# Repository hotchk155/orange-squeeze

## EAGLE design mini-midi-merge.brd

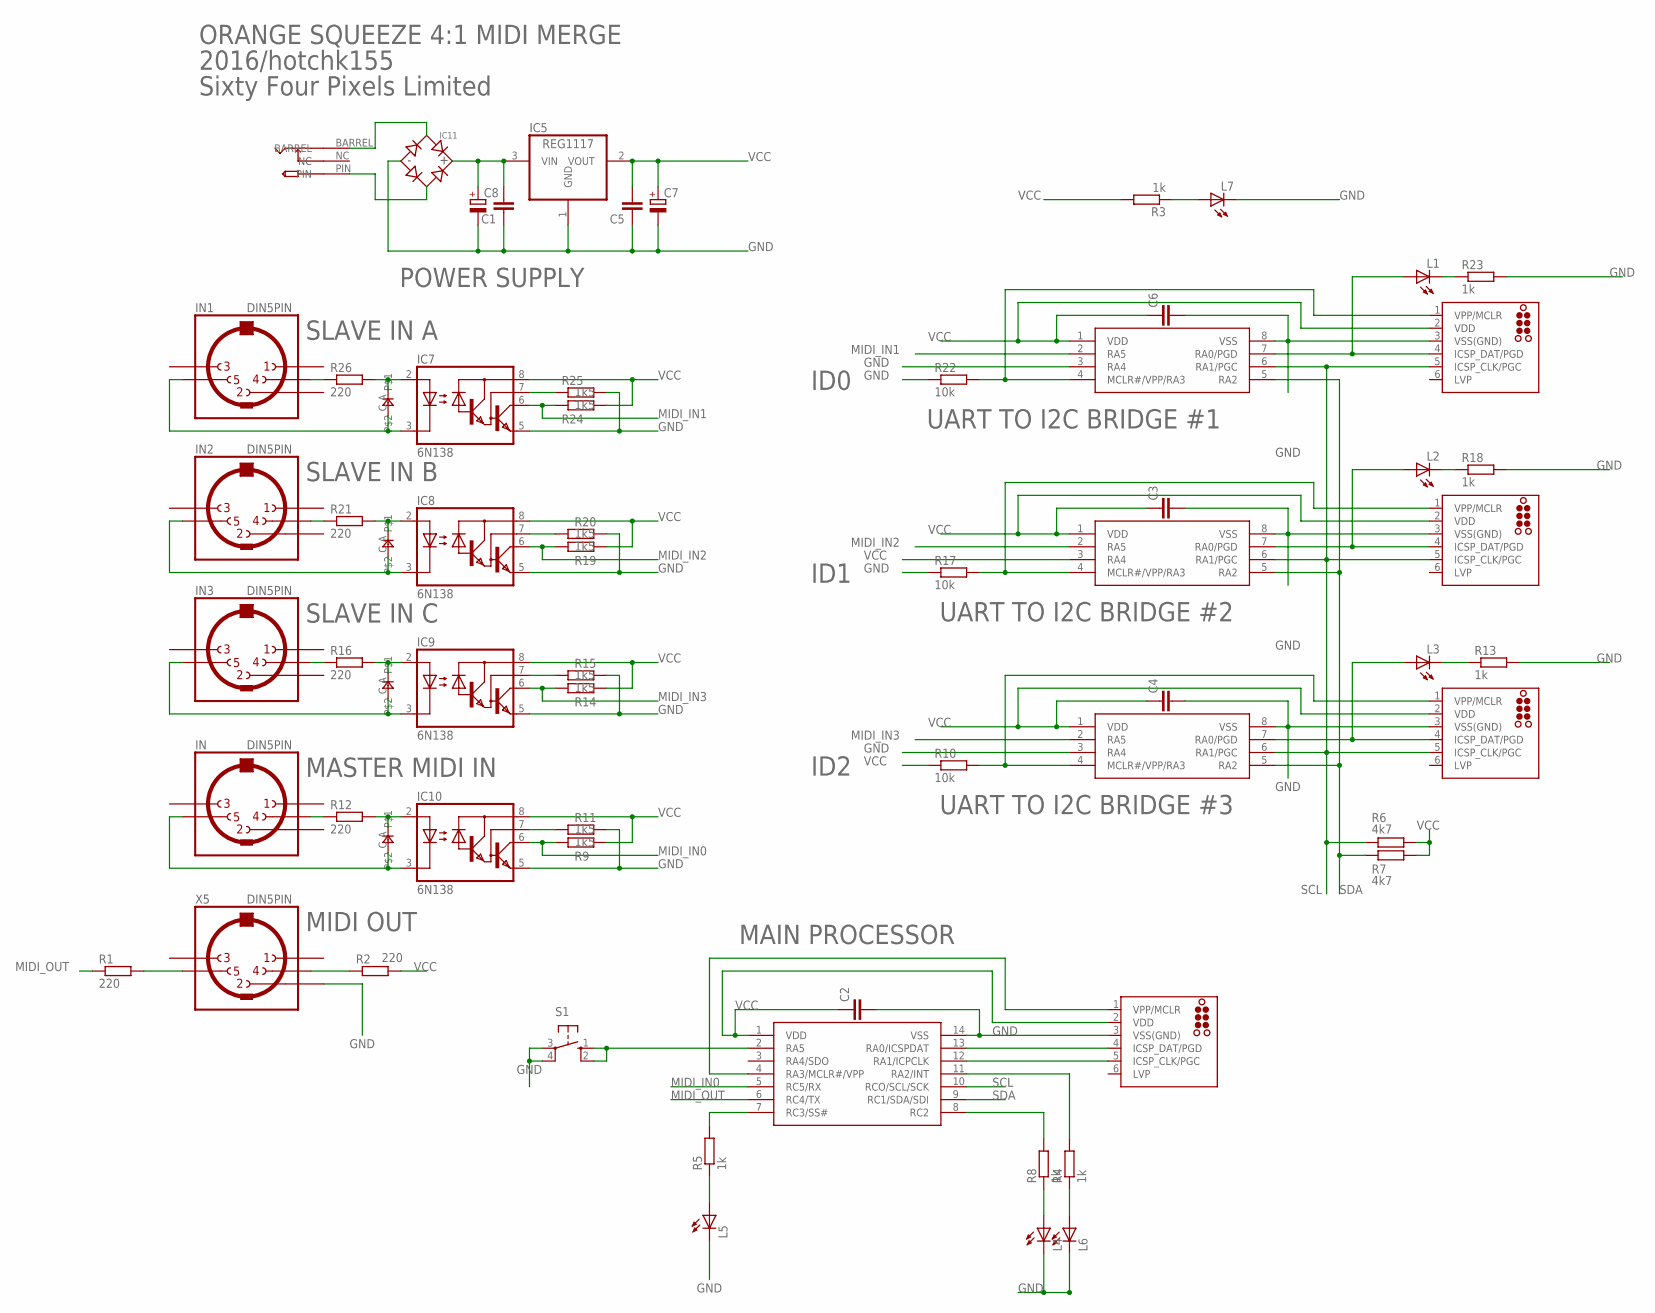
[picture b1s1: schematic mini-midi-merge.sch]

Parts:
C1, C2, C3, C4, C5, C6: C-EUC0805; C0805
C7, C8: CPOL-EUE2,5-6E; E2,5-6E
D1, D2, D3, D4: 0805DIODE
IC1: PIC16F1825SO14; SO14
IC2, IC3, IC4: PIC12F1822SO08; SO08
IC5: REG1117; SOT223
IC7, IC8, IC9, IC10: 6N138; DIL08
IC11: BRIDGERECTIFIER; SOIC-4
ICSP1, ICSP2, ICSP3, ICSP4: TC2030-MCP-NL
IN, IN1, IN2, IN3: DIN5PIN; EDGEDIN
L1, L2, L3, L4, L5, L6, L7: LED3MM
R1, R2, R12, R16, R21, R26: 220; R0805
R3, R4, R5, R8, R13, R18, R23: 1k; R0805
R6, R7: 4k7; R0805
R9, R11, R14, R15, R19, R20, R24, R25: 1k5; R0805
R10, R17, R22: 10k; R0805
S1: 10-XX; B3F-10XX
U$9: PWR_SOCKET_2_1MM
X5: DIN5PIN; EDGEDIN

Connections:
GND: C1.1, C2.2, C3.2, C4.2, C5.1, C6.2, C7.-, C8.-, IC1.14 (VSS), IC2.3 (RA4), IC2.8 (VSS), IC3.8 (VSS), IC4.3 (RA4), IC4.8 (VSS), IC5.1 (GND), IC7.5 (GND), IC8.5 (GND), IC9.5 (GND), IC10.5 (GND), IC11.-, ICSP1.3 (VSS(GND)), ICSP2.3 (VSS(GND)), ICSP3.3 (VSS(GND)), ICSP4.3 (VSS(GND)), L4.K (C), L5.K (C), L6.K (C), L7.K (C), R11.2, R13.2, R15.2, R17.1, R18.2, R20.2, R22.1, R23.2, R25.2, S1.3, S1.4 (P1), X5.2
MIDI_IN0: IC1.5 (RC5/RX), IC10.6 (VO), R9.1
MIDI_IN1: IC4.2 (RA5), IC7.6 (VO), R24.1
MIDI_IN2: IC3.2 (RA5), IC8.6 (VO), R19.1
MIDI_IN3: IC2.2 (RA5), IC9.6 (VO), R14.1
MIDI_OUT: IC1.6 (RC4/TX), R1.1
unnamed: IN3.4, R16.1
unnamed: D2.A, IC9.2 (A), R16.2
unnamed: D2.C, IC9.3 (C), IN3.5
unnamed: IN2.4, R21.1
unnamed: IC9.7 (VB), R15.1
unnamed: D3.A, IC8.2 (A), R21.2
unnamed: D3.C, IC8.3 (C), IN2.5
unnamed: IC8.7 (VB), R20.1
unnamed: IN1.4, R26.1
unnamed: D4.A, IC7.2 (A), R26.2
unnamed: D4.C, IC7.3 (C), IN1.5
unnamed: IC7.7 (VB), R25.1
unnamed: IN.4, R12.1
unnamed: D1.A, IC10.2 (A), R12.2
unnamed: D1.C, IC10.3 (C), IN.5
unnamed: IC10.7 (VB), R11.1
unnamed: IC3.4 (MCLR#/VPP/RA3), ICSP3.1 (VPP/MCLR), R17.2
unnamed: IC4.4 (MCLR#/VPP/RA3), ICSP4.1 (VPP/MCLR), R22.2
unnamed: L4.A, R8.1
unnamed: C1.2, C8.+, IC5.3 (VIN), IC11.+
unnamed: L7.A, R3.1
unnamed: R1.2, X5.5
unnamed: IC4.7 (RA0/PGD), ICSP4.4 (ICSP_DAT/PGD), L1.A
unnamed: L1.K (C), R23.1
unnamed: IC2.7 (RA0/PGD), ICSP2.4 (ICSP_DAT/PGD), L3.A
unnamed: L2.K (C), R18.1
unnamed: IC2.4 (MCLR#/VPP/RA3), ICSP2.1 (VPP/MCLR), R10.2
unnamed: R2.1, X5.4
unnamed: IC3.7 (RA0/PGD), ICSP3.4 (ICSP_DAT/PGD), L2.A
unnamed: L3.K (C), R13.1
unnamed: IC1.4 (RA3/MCLR#/VPP), ICSP1.1 (VPP/MCLR)
unnamed: L6.A, R4.1
unnamed: IC1.13 (RA0/ICSPDAT), ICSP1.4 (ICSP_DAT/PGD)
unnamed: IC1.12 (RA1/ICPCLK), ICSP1.5 (ICSP_CLK/PGC)
unnamed: IC1.8 (RC2), R8.2
unnamed: IC1.11 (RA2/INT), R4.2
unnamed: IC11.~1 (AC1), U$9.BARREL
unnamed: IC11.~2 (AC2), U$9.PIN
unnamed: IC1.2 (RA5), S1.1 (S), S1.2 (S1)
unnamed: IC1.7 (RC3/SS#), R5.2
unnamed: L5.A, R5.1
SCL: IC1.10 (RCO/SCL/SCK), IC2.6 (RA1/PGC), IC3.6 (RA1/PGC), IC4.6 (RA1/PGC), ICSP2.5 (ICSP_CLK/PGC), ICSP3.5 (ICSP_CLK/PGC), ICSP4.5 (ICSP_CLK/PGC), R6.1
SDA: IC1.9 (RC1/SDA/SDI), IC2.5 (RA2), IC3.5 (RA2), IC4.5 (RA2), R7.1
VCC: C2.1, C3.1, C4.1, C5.2, C6.1, C7.+, IC1.1 (VDD), IC2.1 (VDD), IC3.1 (VDD), IC3.3 (RA4), IC4.1 (VDD), IC5.2 (VOUT), IC7.8 (VCC), IC8.8 (VCC), IC9.8 (VCC), IC10.8 (VCC), ICSP1.2 (VDD), ICSP2.2 (VDD), ICSP3.2 (VDD), ICSP4.2 (VDD), R2.2, R3.2, R6.2, R7.2, R9.2, R10.1, R14.2, R19.2, R24.2

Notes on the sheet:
POWER SUPPLY
UART TO I2C BRIDGE #1
UART TO I2C BRIDGE #2
UART TO I2C BRIDGE #3
MAIN PROCESSOR
SLAVE IN A
SLAVE IN B
SLAVE IN C
MASTER MIDI IN
MIDI OUT
ORANGE SQUEEZE 4:1 MIDI MERGE
2016/hotchk155
Sixty Four Pixels Limited
ID0
ID1
ID2

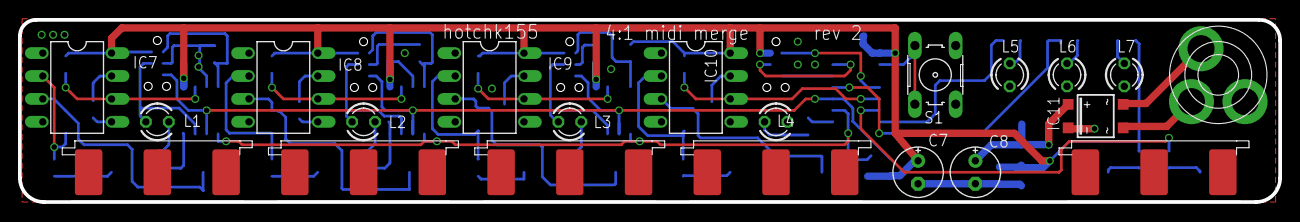
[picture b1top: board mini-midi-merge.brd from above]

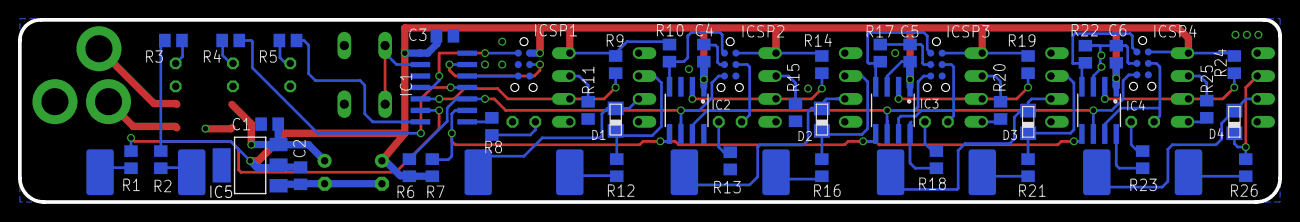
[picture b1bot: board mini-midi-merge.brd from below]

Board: 2 copper layers, 139.7 x 20.2 mm, 66 parts (45 on the bottom side), 50 nets.

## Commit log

2016-02-09 :space_invader: Added .gitattributes & .gitignore files
2016-02-09 init
2016-02-10 almost done
2016-02-10 ground output pin 2
2016-03-20 adding comp values
2016-03-21 slave baseline
2016-03-21 gitignore
2016-03-21 stuff
2016-06-17 in work
2016-06-19 more
2016-07-09 tidy up schematic
2016-07-09 PCB REV2
    move switch to match bsplit
2016-07-09 reorg
2016-07-09 tidyup
2016-09-04 test release
2016-11-28 tidy
2016-11-28 add rev1 slave
2016-11-28 ignore
2016-11-28 rev1 release candidate
2016-11-29 adding test code
2017-01-15 packing slip
2021-08-02 added orange squeeeze tester

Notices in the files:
parts and their libraries:
tag-connect: ©2009 ROFA.cz - modified and updated by Robert Darlington ‹rdarlington@gmail.com›
